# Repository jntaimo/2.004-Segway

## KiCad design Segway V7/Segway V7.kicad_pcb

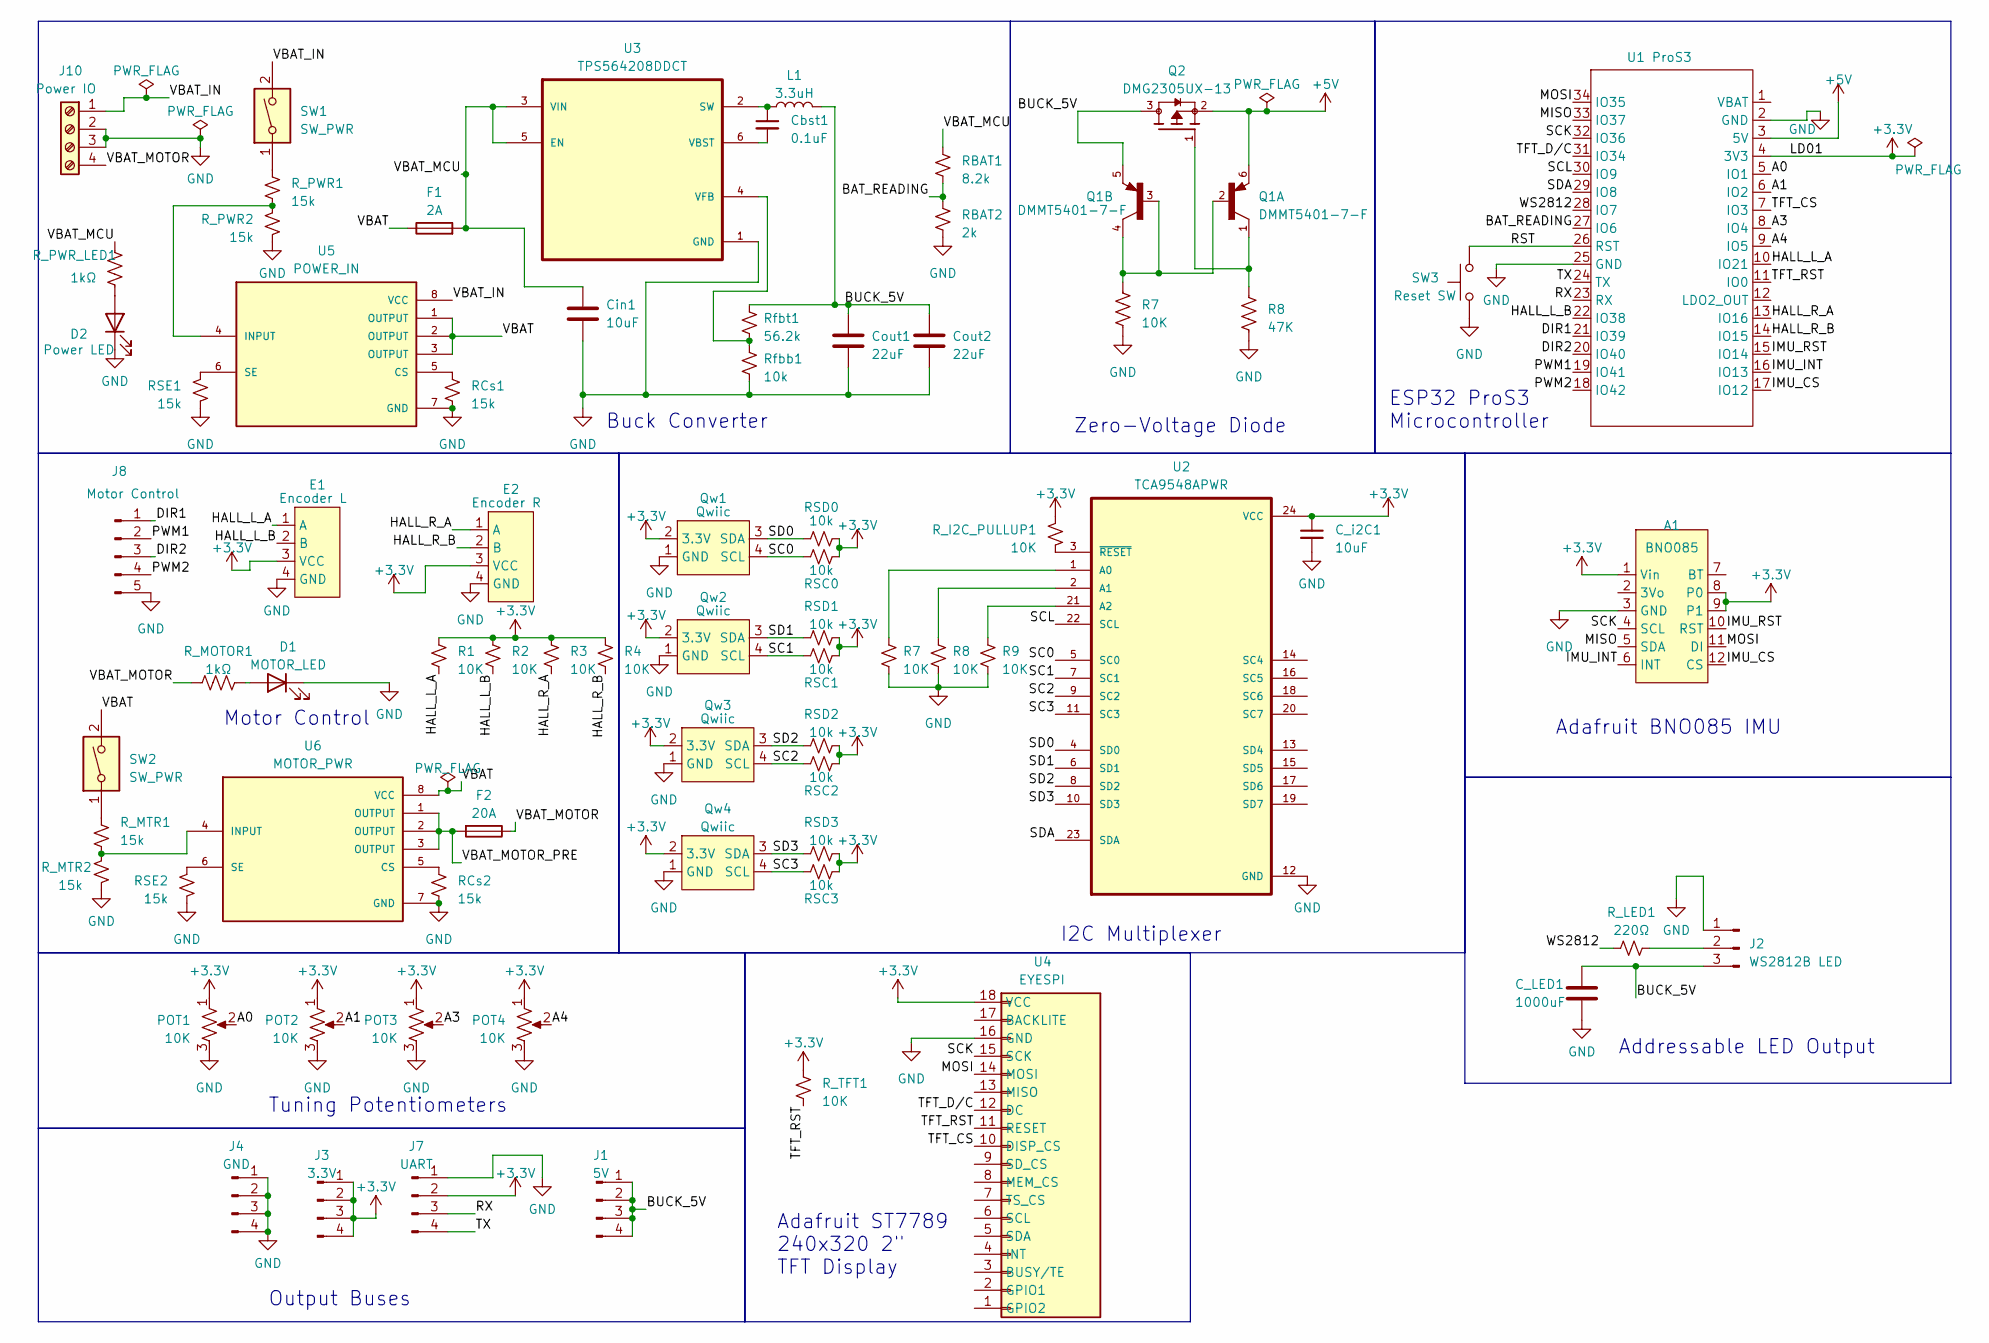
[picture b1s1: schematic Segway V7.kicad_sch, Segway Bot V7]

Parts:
A1: BNO085; Adafruit_BNO085
C_LED1: 1000uF; CP_Elec_10x12.6; MPN C250086
C_i2C1: 10uF; C_0805_2012Metric_Pad1.18x1.45mm_HandSolder; MPN C39232
Cbst1: 0.1uF; C_0805_2012Metric; MPN C519981
Cin1: 10uF; C_1210_3225Metric; MPN C39232
Cout1, Cout2: 22uF; C_1210_3225Metric; MPN C65428
D1: MOTOR_LED; LED_0603_1608Metric; MPN C434423
D2: Power LED; LED_0603_1608Metric; MPN C84263
E1: Encoder L; JST_PH_S4B-PH-SM4-TB_1x04-1MP_P2.00mm_Horizontal; MPN C265102
E2: Encoder R; JST_PH_S4B-PH-SM4-TB_1x04-1MP_P2.00mm_Horizontal; MPN C265102
F1: 2A; Fuse_1206_3216Metric; MPN C355683
F2: 20A; Fuse_1206_3216Metric; MPN C207007
J1: 5V; PinHeader_1x04_P2.54mm_Vertical
J2: WS2812B LED; PinHeader_1x03_P2.54mm_Vertical
J3: 3.3V; PinHeader_1x04_P2.54mm_Vertical
J4: GND; PinHeader_1x04_P2.54mm_Vertical
J7: UART; PinHeader_1x04_P2.54mm_Vertical
J8: Motor Control; PinHeader_1x05_P2.54mm_Vertical
J10: Power IO; TerminalBlock_Phoenix_MKDS-3-4-5.08_1x04_P5.08mm_Horizontal; MPN C3816378
L1: 3.3uH; L_Vishay_IHLP-4040; MPN C845075
POT1, POT2, POT3, POT4: 10K; JST_PH_B3B-PH-SM4-TB_1x03-1MP_P2.00mm_Vertical; MPN C265082
Q1: DMMT5401-7-F; SOT95P285X140-6N; PARTREV 8
Q2: DMG2305UX-13; SOT91P240X110-3N; PARTREV 09/2018
Qw1, Qw2, Qw3, Qw4: Qwiic; JST_SH_BM04B-SRSS-TB_1x04-1MP_P1.00mm_Vertical; MPN C160390
R1, R2, R3, R4, R7, R9: 10K; R_0402_1005Metric; MPN C144807
R8: 47K; R_0402_1005Metric; MPN C25792
RBAT1: 8.2k; R_0402_1005Metric; MPN C25924
RBAT2: 2k; R_0402_1005Metric; MPN C4109
RCs1, RCs2: 15k; R_0402_1005Metric; MPN C25756
RSC0, RSC1, RSC2, RSC3: 10k; R_0402_1005Metric; MPN C144807
RSD0, RSD1, RSD2, RSD3: 10k; R_0402_1005Metric; MPN C144807
RSE1, RSE2: 15k; R_0402_1005Metric; MPN C25756
R_I2C_PULLUP1: 10K; R_0402_1005Metric; MPN C144807
R_LED1: 220Ω; R_0402_1005Metric; MPN C25151
R_MOTOR1: 1kΩ; R_0402_1005Metric; MPN C21190
R_MTR1, R_MTR2: 15k; R_0402_1005Metric; MPN C25756
R_PWR1, R_PWR2: 15k; R_0402_1005Metric; MPN C25756
R_PWR_LED1: 1kΩ; R_0402_1005Metric; MPN C21190
R_TFT1: 10K; R_0402_1005Metric; MPN C144807
Rfbb1: 10k; R_0402_1005Metric; MPN C144807
Rfbt1: 56.2k; R_0402_1005Metric; MPN C183355
SW1, SW2: SW_PWR; JST_PH_B2B-PH-SM4-TB_1x02-1MP_P2.00mm_Vertical; MPN C160352
SW3: Reset SW; SW_PUSH_6mm
U1: ProS3; ProS3_TH
U2: TCA9548APWR; SOP65P640X120-24N; MPN C130026
U3: TPS564208DDCT; SOT95P280X110-6N; MPN C2070774
U4: EYESPI; Hirose_FH12-18S-0.5SH_1x18-1MP_P0.50mm_Horizontal; MPN C2856802
U5: POWER_IN; DPAK85P972X240-8N; MPN C2150194
U6: MOTOR_PWR; DPAK85P972X240-8N; MPN C2150194

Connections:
+3.3V: A1.1 (Vin), A1.8 (P0), A1.9 (P1), C_i2C1.1, E1.3 (VCC), E2.3 (VCC), J3.1, J3.2, J3.3, J3.4, J7.2, POT1.1, POT2.1, POT3.1, POT4.1, Qw1.2 (3.3V), Qw2.2 (3.3V), Qw3.2 (3.3V), Qw4.2 (3.3V), R1.1, R2.1, R3.1, R4.1, RSC0.2, RSC1.2, RSC2.2, RSC3.2, RSD0.2, RSD1.2, RSD2.2, RSD3.2, R_I2C_PULLUP1.1, R_TFT1.1, U1.4 (3V3), U2.24 (VCC), U4.18 (VCC)
+5V: Q1.6, Q2.2, U1.3 (5V)
/A0: POT1.2, U1.5 (IO1)
/A1: POT2.2, U1.6 (IO2)
/A3: POT3.2, U1.8 (IO4)
/A4: POT4.2, U1.9 (IO5)
/BAT_READING: RBAT1.2, RBAT2.1, U1.27 (IO6)
/BUCK_5V: C_LED1.1, Cout1.1, Cout2.1, J1.1, J1.2, J1.3, J1.4, J2.3, L1.2, Q1.5, Q2.3, Rfbt1.1
/DIR1: J8.1, U1.21 (IO39)
/DIR2: J8.3, U1.20 (IO40)
/HALL_L_A: E1.1 (A), R1.2, U1.10 (IO21)
/HALL_L_B: E1.2 (B), R2.2, U1.22 (IO38)
/HALL_R_A: E2.1 (A), R3.2, U1.13 (IO16)
/HALL_R_B: E2.2 (B), R4.2, U1.14 (IO15)
/IMU_CS: A1.12 (CS), U1.17 (IO12)
/IMU_INT: A1.6 (INT), U1.16 (IO13)
/IMU_RST: A1.10 (RST), U1.15 (IO14)
/MISO: A1.5 (SDA), U1.33 (IO37)
/MOSI: A1.11 (DI), U1.34 (IO35), U4.14 (MOSI)
/PWM1: J8.2, U1.19 (IO41)
/PWM2: J8.4, U1.18 (IO42)
/RST: SW3.1, U1.26 (RST)
/RX: J7.3, U1.23 (RX)
/SC0: Qw1.4 (SCL), RSC0.1, U2.5 (SC0)
/SC1: Qw2.4 (SCL), RSC1.1, U2.7 (SC1)
/SC2: Qw3.4 (SCL), RSC2.1, U2.9 (SC2)
/SC3: Qw4.4 (SCL), RSC3.1, U2.11 (SC3)
/SCK: A1.4 (SCL), U1.32 (IO36), U4.15 (SCK)
/SCL: U1.30 (IO9), U2.22 (SCL)
/SD0: Qw1.3 (SDA), RSD0.1, U2.4 (SD0)
/SD1: Qw2.3 (SDA), RSD1.1, U2.6 (SD1)
/SD2: Qw3.3 (SDA), RSD2.1, U2.8 (SD2)
/SD3: Qw4.3 (SDA), RSD3.1, U2.10 (SD3)
/SDA: U1.29 (IO8), U2.23 (SDA)
/TFT_CS: U1.7 (IO3), U4.10 (DISP_CS)
/TFT_D/C: U1.31 (IO34), U4.12 (DC)
/TFT_RST: R_TFT1.2, U1.11 (IO0), U4.11 (RESET)
/TX: J7.4, U1.24 (TX)
/VBAT: F1.1, SW2.2, U5.1 (OUTPUT), U5.2 (OUTPUT), U5.3 (OUTPUT), U6.8 (VCC)
/VBAT_IN: J10.1, SW1.2, U5.8 (VCC)
/VBAT_MCU: Cin1.1, F1.2, RBAT1.1, R_PWR_LED1.2, U3.3 (VIN), U3.5 (EN)
/VBAT_MOTOR: F2.1, J10.4, R_MOTOR1.1
/VBAT_MOTOR_PRE: F2.2, U6.1 (OUTPUT), U6.2 (OUTPUT), U6.3 (OUTPUT)
/WS2812: R_LED1.1, U1.28 (IO7)
GND: A1.3 (GND), C_LED1.2, C_i2C1.2, Cin1.2, Cout1.2, Cout2.2, D1.1 (K), D2.1 (K), E1.4 (GND), E2.4 (GND), J2.1, J4.1, J4.2, J4.3, J4.4, J7.1, J8.5, J10.2, J10.3, POT1.3, POT2.3, POT3.3, POT4.3, Qw1.1 (GND), Qw2.1 (GND), Qw3.1 (GND), Qw4.1 (GND), R7.2, R8.2, R9.2, RBAT2.2, RCs1.2, RCs2.2, RSE1.2, RSE2.2, R_MTR2.2, R_PWR2.2, Rfbb1.2, SW3.2, U1.2 (GND), U1.25 (GND), U2.12 (GND), U3.1 (GND), U4.16 (GND), U5.7 (GND), U6.7 (GND); also elsewhere on the board
unnamed: D1.2 (A), R_MOTOR1.2
unnamed: D2.2 (A), R_PWR_LED1.1
unnamed: J2.2, R_LED1.2
unnamed: R_MTR1.1, SW2.1
unnamed: R_PWR1.1, SW1.1
unnamed: R9.1, U2.21 (A2)
unnamed: R_I2C_PULLUP1.2, U2.3 (~RESET)
unnamed: Cbst1.1, L1.1, U3.2 (SW)
unnamed: Cbst1.2, U3.6 (VBST)
unnamed: Rfbb1.1, Rfbt1.2, U3.4 (VFB)
unnamed: RCs1.1, U5.5 (CS)
unnamed: R_PWR1.2, R_PWR2.1, U5.4 (INPUT)
unnamed: RSE1.1, U5.6 (SE)
unnamed: RCs2.1, U6.5 (CS)
unnamed: R_MTR1.2, R_MTR2.1, U6.4 (INPUT)
unnamed: RSE2.1, U6.6 (SE)

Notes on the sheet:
Motor Control
Output Buses
Zero-Voltage Diode
Adafruit ST7789 240x320 2" TFT Display
ESP32 ProS3 Microcontroller
I2C Multiplexer
Tuning Potentiometers
Buck Converter
Adafruit BNO085 IMU
Addressable LED Output

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
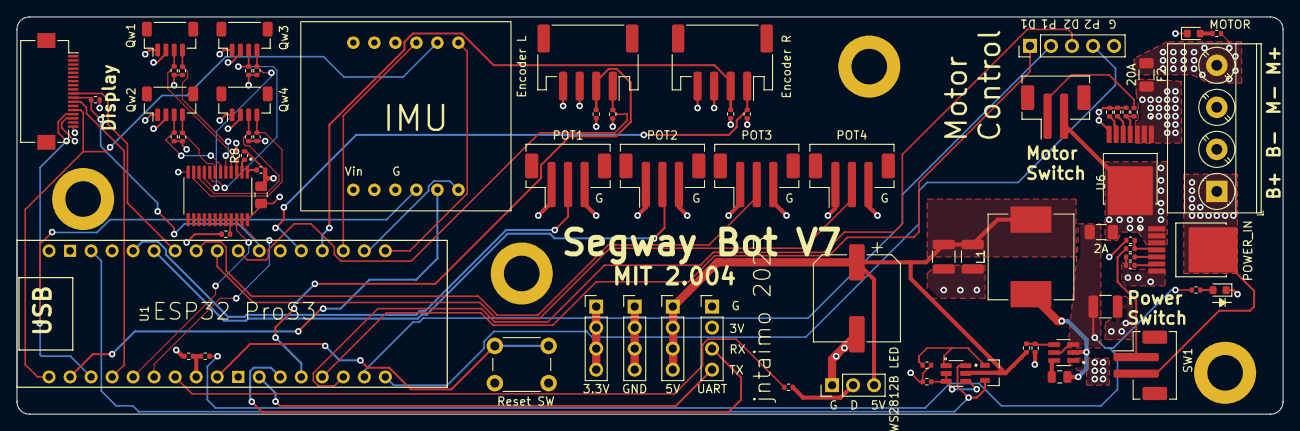
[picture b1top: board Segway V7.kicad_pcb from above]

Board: 4 copper layers, 153.0 x 48.0 mm, 74 parts (0 on the bottom side), 65 nets.

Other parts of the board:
R_ZVD_1: 10K; R_0402_1005Metric
R_ZVD_2: 47K; R_0402_1005Metric

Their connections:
GND: R_ZVD_1.2, R_ZVD_2.2; also elsewhere on the board

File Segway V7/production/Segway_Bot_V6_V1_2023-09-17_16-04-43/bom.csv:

Designator,Footprint,Quantity,Value,LCSC Part #
A1,Adafruit_BNO085,1,BNO085,
C_LED1,CP_Radial_D10.0mm_P5.00mm,1,1000uF,
C_i2C1,0805,1,10uF,C39232
Cbst1,0805,1,0.1uF,C519981
Cin1,1210,1,10uF,C39232
"Cout1, Cout2",1210,2,22uF,C65428
D1,0603,1,MOTOR_LED,C434423
D2,0603,1,Power LED,C84263
E1,JST_PH_S4B-PH-SM4-TB_1x04-1MP_P2.00mm_Horizontal,1,Encoder L,C265116
E2,JST_PH_S4B-PH-SM4-TB_1x04-1MP_P2.00mm_Horizontal,1,Encoder R,C265116
F1,1206,1,2A,C355683
F2,1206,1,20A,C207007
J10,TerminalBlock_Phoenix_MKDS-3-4-5.08_1x04_P5.08mm_Horizontal,1,Power IO,
J2,PinHeader_1x03_P2.54mm_Vertical,1,WS2812B LED,
J3,PinHeader_1x04_P2.54mm_Vertical,1,3.3V,
J4,PinHeader_1x04_P2.54mm_Vertical,1,GND,
J5,PinHeader_1x04_P2.54mm_Vertical,1,5V,
J6,PinHeader_1x04_P2.54mm_Vertical,1,I2C,
J7,PinHeader_1x04_P2.54mm_Vertical,1,UART,
J8,PinHeader_1x05_P2.54mm_Vertical,1,Motor Control,
L1,L_Vishay_IHLP-4040,1,3.3uH,C845075
Q1,SOT95P285X140-6N,1,DMMT5401-7-F,C154733
Q2,SOT91P240X110-3N,1,DMG2305UX-13,C144153
"Qw1, Qw2, Qw3, Qw4",JST_SH_BM04B-SRSS-TB_1x04-1MP_P1.00mm_Vertical,4,Qwiic,C160390
"R1, R2, R3, R4, R7, R8, R9, RSC0, RSC1, RSC2, RSC3, RSD0, RSD1, RSD2, RSD3, R_I2C_PULLUP1, R_TFT1, R_ZVD_1, Rfbb1",0402,19,10K,C60490
RBAT1,0402,1,8.2k,C25924
RBAT2,0402,1,2k,C4109
"RCs1, RCs2, RSE1, RSE2, R_MTR1, R_MTR2, R_PWR1, R_PWR2",0402,8,15k,C25756
"R_LED1, R_MOTOR1, R_PWR_LED1",0402,3,1kΩ,C21190
R_ZVD_2,0402,1,47K,C25792
Rfbt1,0402,1,56.2k,C183355
"SW1, SW2",JST_PH_B2B-PH-SM4-TB_1x02-1MP_P2.00mm_Vertical,2,SW_PWR,C160352
SW3,SW_PUSH_6mm,1,Reset SW,
U1,ProS3_TH,1,ProS3,
U2,SOP65P640X120-24N,1,TCA9548APWR,C130026
U3,SOT95P280X110-6N,1,TPS564208DDCT,C2070774
U4,Hirose_FH12-18S-0.5SH_1x18-1MP_P0.50mm_Horizontal,1,EYESPI,C2856802
U5,DPAK85P972X240-8N,1,POWER_IN,C2150194
U6,DPAK85P972X240-8N,1,MOTOR_PWR,C2150194

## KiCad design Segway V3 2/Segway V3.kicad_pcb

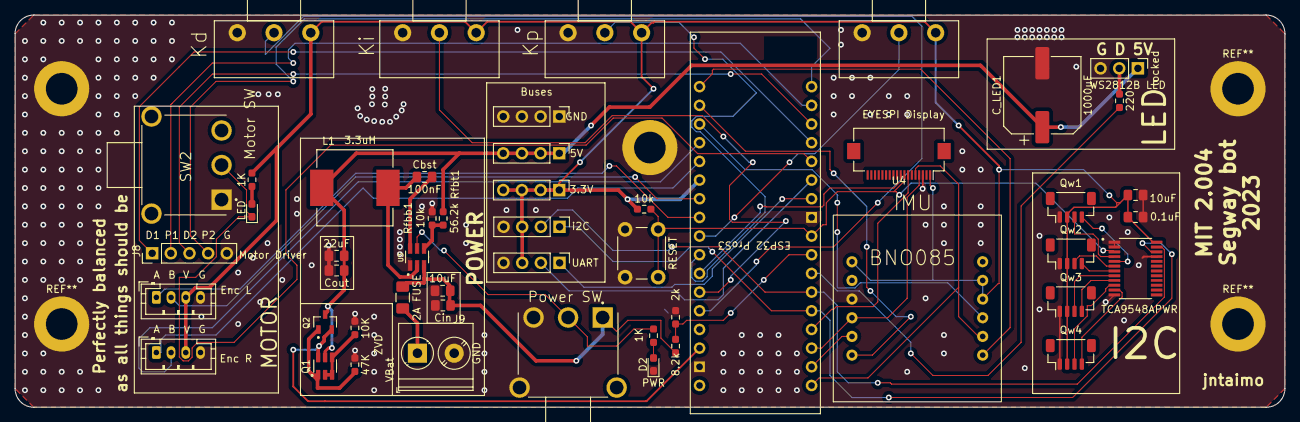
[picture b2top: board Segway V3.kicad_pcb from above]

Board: 2 copper layers, 172.7 x 53.3 mm, 50 parts (0 on the bottom side), 51 nets.

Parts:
2A FUSE: 2A; Fuse_1206_3216Metric_Pad1.42x1.75mm_HandSolder
3.3V: 3.3V_BUS; PinHeader_1x04_P2.54mm_Vertical
5V: 5V_BUS; PinHeader_1x04_P2.54mm_Vertical
10uF: 10uF; C_0805_2012Metric_Pad1.18x1.45mm_HandSolder
A1: BNO085; Adafruit_BNO085
C_LED1: 1000uF; CP_Elec_10x7.9
C_i2C2: 0.1uF; C_0805_2012Metric_Pad1.18x1.45mm_HandSolder
Cbst: 100nF; C_0805_2012Metric_Pad1.18x1.45mm_HandSolder
Cin, Cin2: 10uF; C_0805_2012Metric_Pad1.18x1.45mm_HandSolder
Cout, Cout2: 22uF; C_0805_2012Metric_Pad1.18x1.45mm_HandSolder
D2: PWR; LED_0603_1608Metric_Pad1.05x0.95mm_HandSolder
E1: Enc L; JST_PH_B4B-PH-K_1x04_P2.00mm_Vertical
E2: Enc R; JST_PH_B4B-PH-K_1x04_P2.00mm_Vertical
ESP32 ProS3: ProS3; ProS3_TH
GND: GND_BUS; PinHeader_1x04_P2.54mm_Vertical
J8: Motor Driver; PinHeader_1x05_P2.54mm_Vertical
J9: Power Input; TerminalBlock_Phoenix_PT-1,5-2-5.0-H_1x02_P5.00mm_Horizontal
Kd: 10K; Pot_breadboard
Ki: 10K; Pot_breadboard
Kp: 10K; Pot_breadboard
L1: 3.3uH; L_Vishay_IHLP-4040
LED: MOTOR_LED; LED_0603_1608Metric_Pad1.05x0.95mm_HandSolder
POT4: 10K; Pot_breadboard
Q1: DMMT5401; SOT95P285X140-6N
Q2: DMG2305UX-13; SOT91P240X110-3N
Qw1, Qw2, Qw3, Qw4: Qwiic; JST_SH_BM04B-SRSS-TB_1x04-1MP_P1.00mm_Vertical
RBAT1: 8.2k; R_0603_1608Metric_Pad0.98x0.95mm_HandSolder
RBAT2: 2k; R_0603_1608Metric_Pad0.98x0.95mm_HandSolder
RESET: Reset SW; SW_PUSH_6mm
R_LED1: 220; R_0603_1608Metric_Pad0.98x0.95mm_HandSolder
R_MOTOR1: 1K; R_0603_1608Metric_Pad0.98x0.95mm_HandSolder
R_PWR1: 1K; R_0603_1608Metric_Pad0.98x0.95mm_HandSolder
R_RESET1: 10k; R_0603_1608Metric_Pad0.98x0.95mm_HandSolder
R_ZVD_1: 10K; R_0603_1608Metric_Pad0.98x0.95mm_HandSolder
R_ZVD_2: 47K; R_0603_1608Metric_Pad0.98x0.95mm_HandSolder
Rfbb1: 10k; R_0603_1608Metric_Pad0.98x0.95mm_HandSolder
Rfbt1: 56.2k; R_0603_1608Metric_Pad0.98x0.95mm_HandSolder
S1: Power SW; SW_500SSP1S1M6QEA
SW2: Motor SW; SW_500SSP1S1M6QEA
U2: TCA9548APWR; SOP65P640X120-24N
U3: TPS564208DDCT; SOT95P280X110-6N
U4: EYESPI Display; Hirose_FH12-18S-0.5SH_1x18-1MP_P0.50mm_Horizontal
UART: UART; PinHeader_1x04_P2.54mm_Vertical
i2C: I2C; PinHeader_1x04_P2.54mm_Vertical
locked: WS2812B LED; PinHeader_1x03_P2.54mm_Vertical

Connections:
+3.3V: 3.3V.1, 3.3V.2, 3.3V.3, 3.3V.4, 10uF.1, A1.1 (Vin), A1.8 (P0), A1.9 (P1), C_i2C2.1, E1.3 (VCC), E2.3 (VCC), ESP32 ProS3.12 (LDO2_OUT), Kd.1, Ki.1, Kp.1, POT4.1, Qw1.2 (3.3V), Qw2.2 (3.3V), Qw3.2 (3.3V), Qw4.2 (3.3V), R_MOTOR1.1, R_RESET1.2, U2.24 (VCC), U4.1 (VCC), UART.3, i2C.3
+5V: ESP32 ProS3.3 (5V), Q1.6, Q2.2
/A0: ESP32 ProS3.5 (IO1), Kd.2
/A1: ESP32 ProS3.6 (IO2), Ki.2
/A3: ESP32 ProS3.8 (IO4), Kp.2
/A4: ESP32 ProS3.9 (IO5), POT4.2
/BAT_READING: ESP32 ProS3.27 (IO6), RBAT1.2, RBAT2.1
/BUCK_5V: 5V.1, 5V.2, 5V.3, 5V.4, C_LED1.1, Cout.1, Cout2.1, L1.2, Q1.5, Q2.3, Rfbt1.1, locked.1
/DIR1: ESP32 ProS3.21 (IO39), J8.1
/DIR2: ESP32 ProS3.20 (IO40), J8.3
/HALL_L_A: E1.1 (A), ESP32 ProS3.10 (IO21)
/HALL_L_B: E1.2 (B), ESP32 ProS3.11 (IO0)
/HALL_R_A: E2.1 (A), ESP32 ProS3.13 (IO16)
/HALL_R_B: E2.2 (B), ESP32 ProS3.14 (IO15)
/IMU_CS: A1.12 (CS), ESP32 ProS3.17 (IO12)
/IMU_INT: A1.6 (INT), ESP32 ProS3.16 (IO13)
/IMU_RST: A1.10 (RST), ESP32 ProS3.15 (IO14)
/MISO: A1.5 (SDA), ESP32 ProS3.33 (IO37)
/MOSI: A1.11 (DI), ESP32 ProS3.34 (IO35), U4.5 (MOSI)
/MOTOR_EN: ESP32 ProS3.22 (IO38), LED.1 (K), SW2.2 (B)
/PWM1: ESP32 ProS3.19 (IO41), J8.2
/PWM2: ESP32 ProS3.18 (IO42), J8.4
/PWR_EN: R_PWR1.2, S1.2, U3.5 (EN)
/RST: ESP32 ProS3.26 (RST), RESET.1, R_RESET1.1, U2.3 (~RESET), U4.8 (RESET)
/RX: ESP32 ProS3.23 (RX), UART.2
/SC0: Qw1.4 (SCL), U2.5 (SC0)
/SC1: Qw2.4 (SCL), U2.7 (SC1)
/SC2: Qw3.4 (SCL), U2.9 (SC2)
/SC3: Qw4.4 (SCL), U2.11 (SC3)
/SCK: A1.4 (SCL), ESP32 ProS3.32 (IO36), U4.4 (SCK)
/SCL: ESP32 ProS3.30 (IO9), U2.22 (SCL), i2C.1
/SD0: Qw1.3 (SDA), U2.4 (SD0)
/SD1: Qw2.3 (SDA), U2.6 (SD1)
/SD2: Qw3.3 (SDA), U2.8 (SD2)
/SD3: Qw4.3 (SDA), U2.10 (SD3)
/SDA: ESP32 ProS3.29 (IO8), U2.23 (SDA), i2C.2
/TFT_CS: ESP32 ProS3.7 (IO3), U4.9 (DISP_CS)
/TFT_D/C: ESP32 ProS3.31 (IO34), U4.7 (DC)
/TX: ESP32 ProS3.24 (TX), UART.1
/VBAT: 2A FUSE.2, Cin.1, Cin2.1, RBAT1.1, S1.1, U3.3 (VIN)
/WS2812: ESP32 ProS3.28 (IO7), R_LED1.1
GND: 10uF.2, A1.3 (GND), C_LED1.2, C_i2C2.2, Cin.2, Cin2.2, Cout.2, Cout2.2, D2.1 (K), E1.4 (GND), E2.4 (GND), ESP32 ProS3.2 (GND), ESP32 ProS3.25 (GND), GND.1, GND.2, GND.3, GND.4, J8.5, J9.2, Kd.3, Ki.3, Kp.3, POT4.3, Qw1.1 (GND), Qw2.1 (GND), Qw3.1 (GND), Qw4.1 (GND), RBAT2.2, RESET.2, R_ZVD_1.2, R_ZVD_2.2, Rfbb1.2, S1.3, S1.S2, SW2.1 (A), U2.1 (A0), U2.2 (A1), U2.12 (GND), U2.21 (A2), U3.1 (GND), U4.3 (GND), UART.4, i2C.4, locked.3
unnamed: LED.2 (A), R_MOTOR1.2
unnamed: D2.2 (A), R_PWR1.1
unnamed: R_LED1.2, locked.2
unnamed: 2A FUSE.1, J9.1
unnamed: Q1.1, Q2.1, R_ZVD_2.1
unnamed: Q1.2, Q1.3, Q1.4, R_ZVD_1.1
unnamed: Cbst.1, L1.1, U3.2 (SW)
unnamed: Cbst.2, U3.6 (VBST)
unnamed: Rfbb1.1, Rfbt1.2, U3.4 (VFB)

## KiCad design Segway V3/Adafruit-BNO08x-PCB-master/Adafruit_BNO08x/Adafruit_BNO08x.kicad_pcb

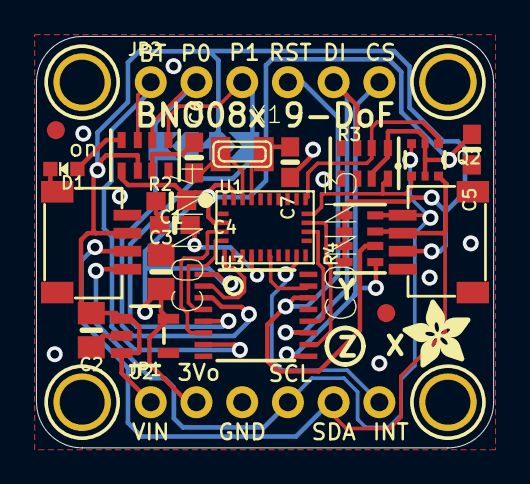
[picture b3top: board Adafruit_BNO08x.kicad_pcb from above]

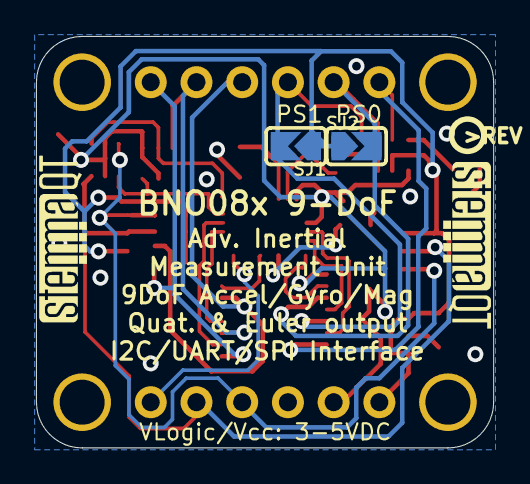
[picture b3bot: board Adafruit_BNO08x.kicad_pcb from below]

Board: 2 copper layers, 25.4 x 22.9 mm, 32 parts (5 on the bottom side), 24 nets.

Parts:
C1, C4, C5: 0.1uF; 0603-NO
C2, C3: 10uF; 0805-NO
C6, C7: 22pF; 0603-NO
CONN3, CONN4: STEMMA_I2C_QT; JST_SH4
D1: GREEN; CHIPLED_0603_NOOUTLINE
FID3, FID4: FIDUCIAL_1MM
JP1, JP2: 1X06_ROUND_70
Q2: BSS138; SOT363
R2, R3, R4: 10K; RESPACK_4X0603
SJ1: PS1; SOLDERJUMPER_ARROW_NOPASTE
SJ2: PS0; SOLDERJUMPER_ARROW_NOPASTE
U1: BNO080
U2: AP2112K-3.3; SOT23-5
U3: 74AHC4050; TSSOP16
U$1, U$17, U$19, U$21: MOUNTINGHOLE2.5; MOUNTINGHOLE_2.5_PLATED
U$22: ADAFRUIT_3.5MM
U$25: PCBFEAT-REV-040
U$30, U$31: STEMMAQT
X1: 32.768; XTAL3215

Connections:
3.3V: C1.1, C3.1, C5.1, JP1.2, Q2.2, Q2.5, R2.5, R3.3, R3.5, U1.3, U1.28, U2.5, U3.1
BOOT: JP2.1, R2.3, U3.7
BOOT_3V: U1.4, U3.6
CAP: C4.2, U1.9
CS: JP2.6, R4.1, U3.9
CS_3V: U1.18, U3.10
GND: C1.2, C2.2, C3.2, C4.1, C5.2, C6.2, C7.2, CONN3.1, CONN3.MT1, CONN3.MT2, CONN4.1, CONN4.MT1, CONN4.MT2, D1.C, JP1.3, R2.7, R2.8, R3.1, R3.2, R3.8, U1.2, U1.10, U1.25, U2.2, U3.8
INT: JP1.6, U1.14
MOSI: JP2.5, R3.7, U3.11
MOSI_3V: U1.17, U3.12
unnamed: D1.A, R2.4
PS0: JP2.2, R2.2, SJ2.2, U3.3
PS0_3V: U1.6, U3.2
PS1: JP2.3, R2.1, SJ1.2, U3.5
PS1_3V: U1.5, U3.4
RST: JP2.4, R4.2, U3.14
RST_3V: U1.11, U3.15
SCL/SCK/RX: CONN3.4, CONN4.4, JP1.4, Q2.6, R4.4
SCL_3V: Q2.1, R3.4, U1.19
SDA/MISO/TX: CONN3.3, CONN4.3, JP1.5, Q2.3, R4.3
SDA_3V: Q2.4, R3.6, U1.20
VCC: C2.1, CONN3.2, CONN4.2, JP1.1, R2.6, R4.5, R4.6, R4.7, R4.8, SJ1.1, SJ2.1, U2.1, U2.3
XIN: C6.1, U1.27, X1.P$1
XOUT: C7.1, U1.26, X1.P$2

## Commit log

2024-01-22 Removed old revisions
